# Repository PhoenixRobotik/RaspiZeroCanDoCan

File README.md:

# RaspiZeroCanDoCAN
A Raspberry Pi Zero (W) Shield to connect it to the PhoenixRobotik "CANdoEverything" bus.
(Raspi is powered by 9V-bus)

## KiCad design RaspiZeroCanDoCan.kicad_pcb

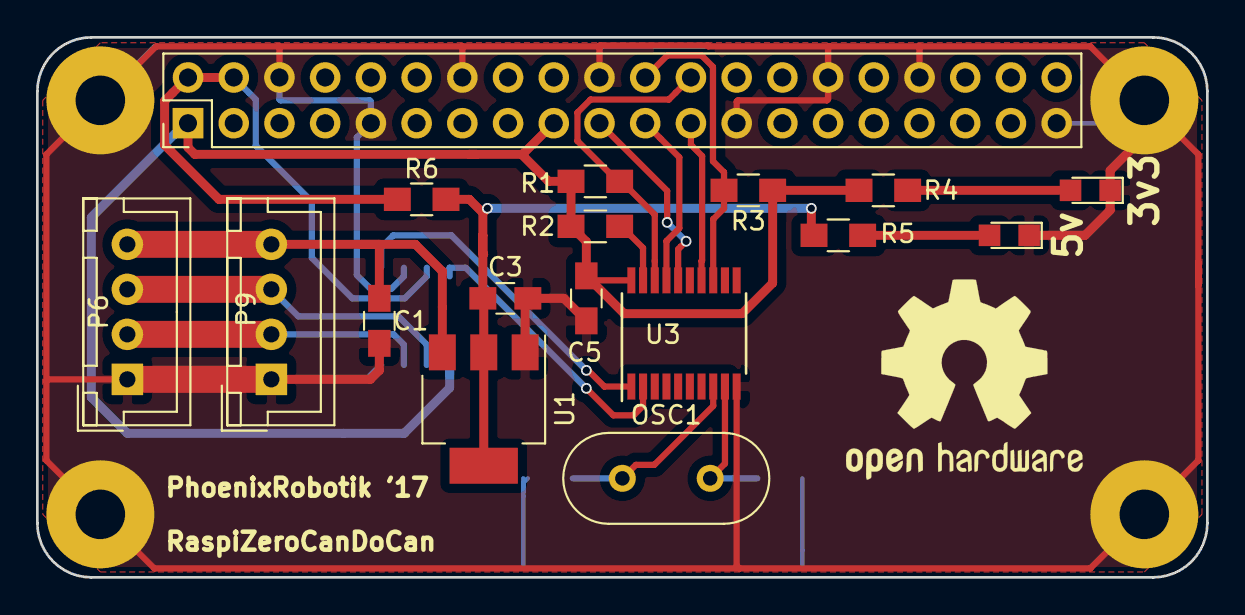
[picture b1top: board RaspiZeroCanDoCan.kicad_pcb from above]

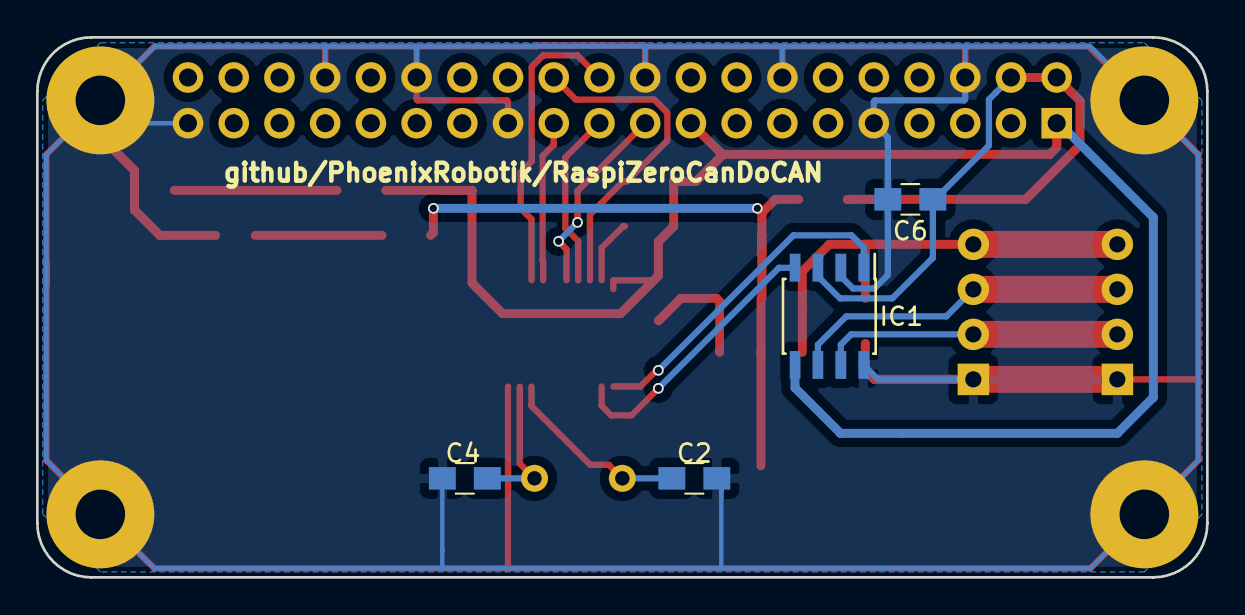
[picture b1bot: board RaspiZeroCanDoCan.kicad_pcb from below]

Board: 2 copper layers, 65.0 x 30.0 mm, 21 parts (4 on the bottom side), 19 nets.

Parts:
C1: 100nF; C_0805_HandSoldering
C2, C4: 22pF; C_0805_HandSoldering
C3: 10uF; C_0805_HandSoldering
C5, C6: C; C_0805_HandSoldering
IC1: MCP2562; SOIC-8_3.9x4.9mm_Pitch1.27mm
LED_3v3_1: 3v3; LED_0805
LED_5v_1: 5v; LED_0805
OSC1: 16MHz; Crystal_HC49-4H_Vertical
P6, P9: CAN_conn; JST_XH_B04B-XH-A_04x2.50mm_Straight
R1, R2, R3: 4k7; R_0805_HandSoldering
R4: 56R; R_0805_HandSoldering
R5: 150R; R_0805_HandSoldering
R6: 0; R_0805_HandSoldering
Raspi1: Raspberry_Pi_2_3; RaspberryPi_Zero_Shield
U1: LD1117S50TR; SOT-223-3Lead_TabPin2
U3: MCP2515-E/ST; TSSOP-20_4.4x6.5mm_Pitch0.65mm

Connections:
+3V3: C5.1, IC1.5, R1.2, R2.1, R3.1, R4.1, Raspi1.1, Raspi1.17, U3.20
+5V: C6.1, IC1.3, R6.1, Raspi1.2, Raspi1.4
+9V: C1.1, P6.4, P9.4, U1.3
CAN_5V: C3.1, R5.1, R6.2, U1.2
CAN_H: IC1.7, P6.2, P9.2
CAN_L: IC1.6, P6.3, P9.3
CAN_RX: IC1.4, U3.2
CAN_TX: IC1.1, U3.1
GND: C1.2, C2.2, C3.2, C4.2, C5.2, C6.2, IC1.2, IC1.8, LED_3v3_1.1, LED_5v_1.1, P6.1, P9.1, Raspi1.6, Raspi1.9, Raspi1.14, Raspi1.20, Raspi1.25, Raspi1.30, Raspi1.34, Raspi1.39, U1.1, U3.10
INT: R3.2, Raspi1.22, U3.13
unnamed: C2.1, OSC1.1, U3.8
unnamed: C4.1, OSC1.2, U3.9
unnamed: LED_3v3_1.2, R4.2
unnamed: LED_5v_1.2, R5.2
unnamed: R2.2, U3.19
SPI_CLK: Raspi1.23, U3.14
SPI_CS0: R1.1, Raspi1.24, U3.18
SPI_MISO: Raspi1.21, U3.17
SPI_MOSI: Raspi1.19, U3.16

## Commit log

2017-03-11 added designs
2017-03-11 added gitignore, licence, readme
2017-03-11 Back from scratch design with power from bus
2017-03-11 removed a capa, cleaned top layer
2017-03-11 pcb refactoring
2017-03-11 fix last commit
2017-03-11 update pcb
2017-03-12 fix footprint, diodes names
2017-03-26 add OSHW logo
2017-04-21 quick fix for MOSI and MISO inversion
2020-10-10 Update to Kicad5
